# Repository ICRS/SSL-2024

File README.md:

# Robocup 2024 SSL Imperial College London

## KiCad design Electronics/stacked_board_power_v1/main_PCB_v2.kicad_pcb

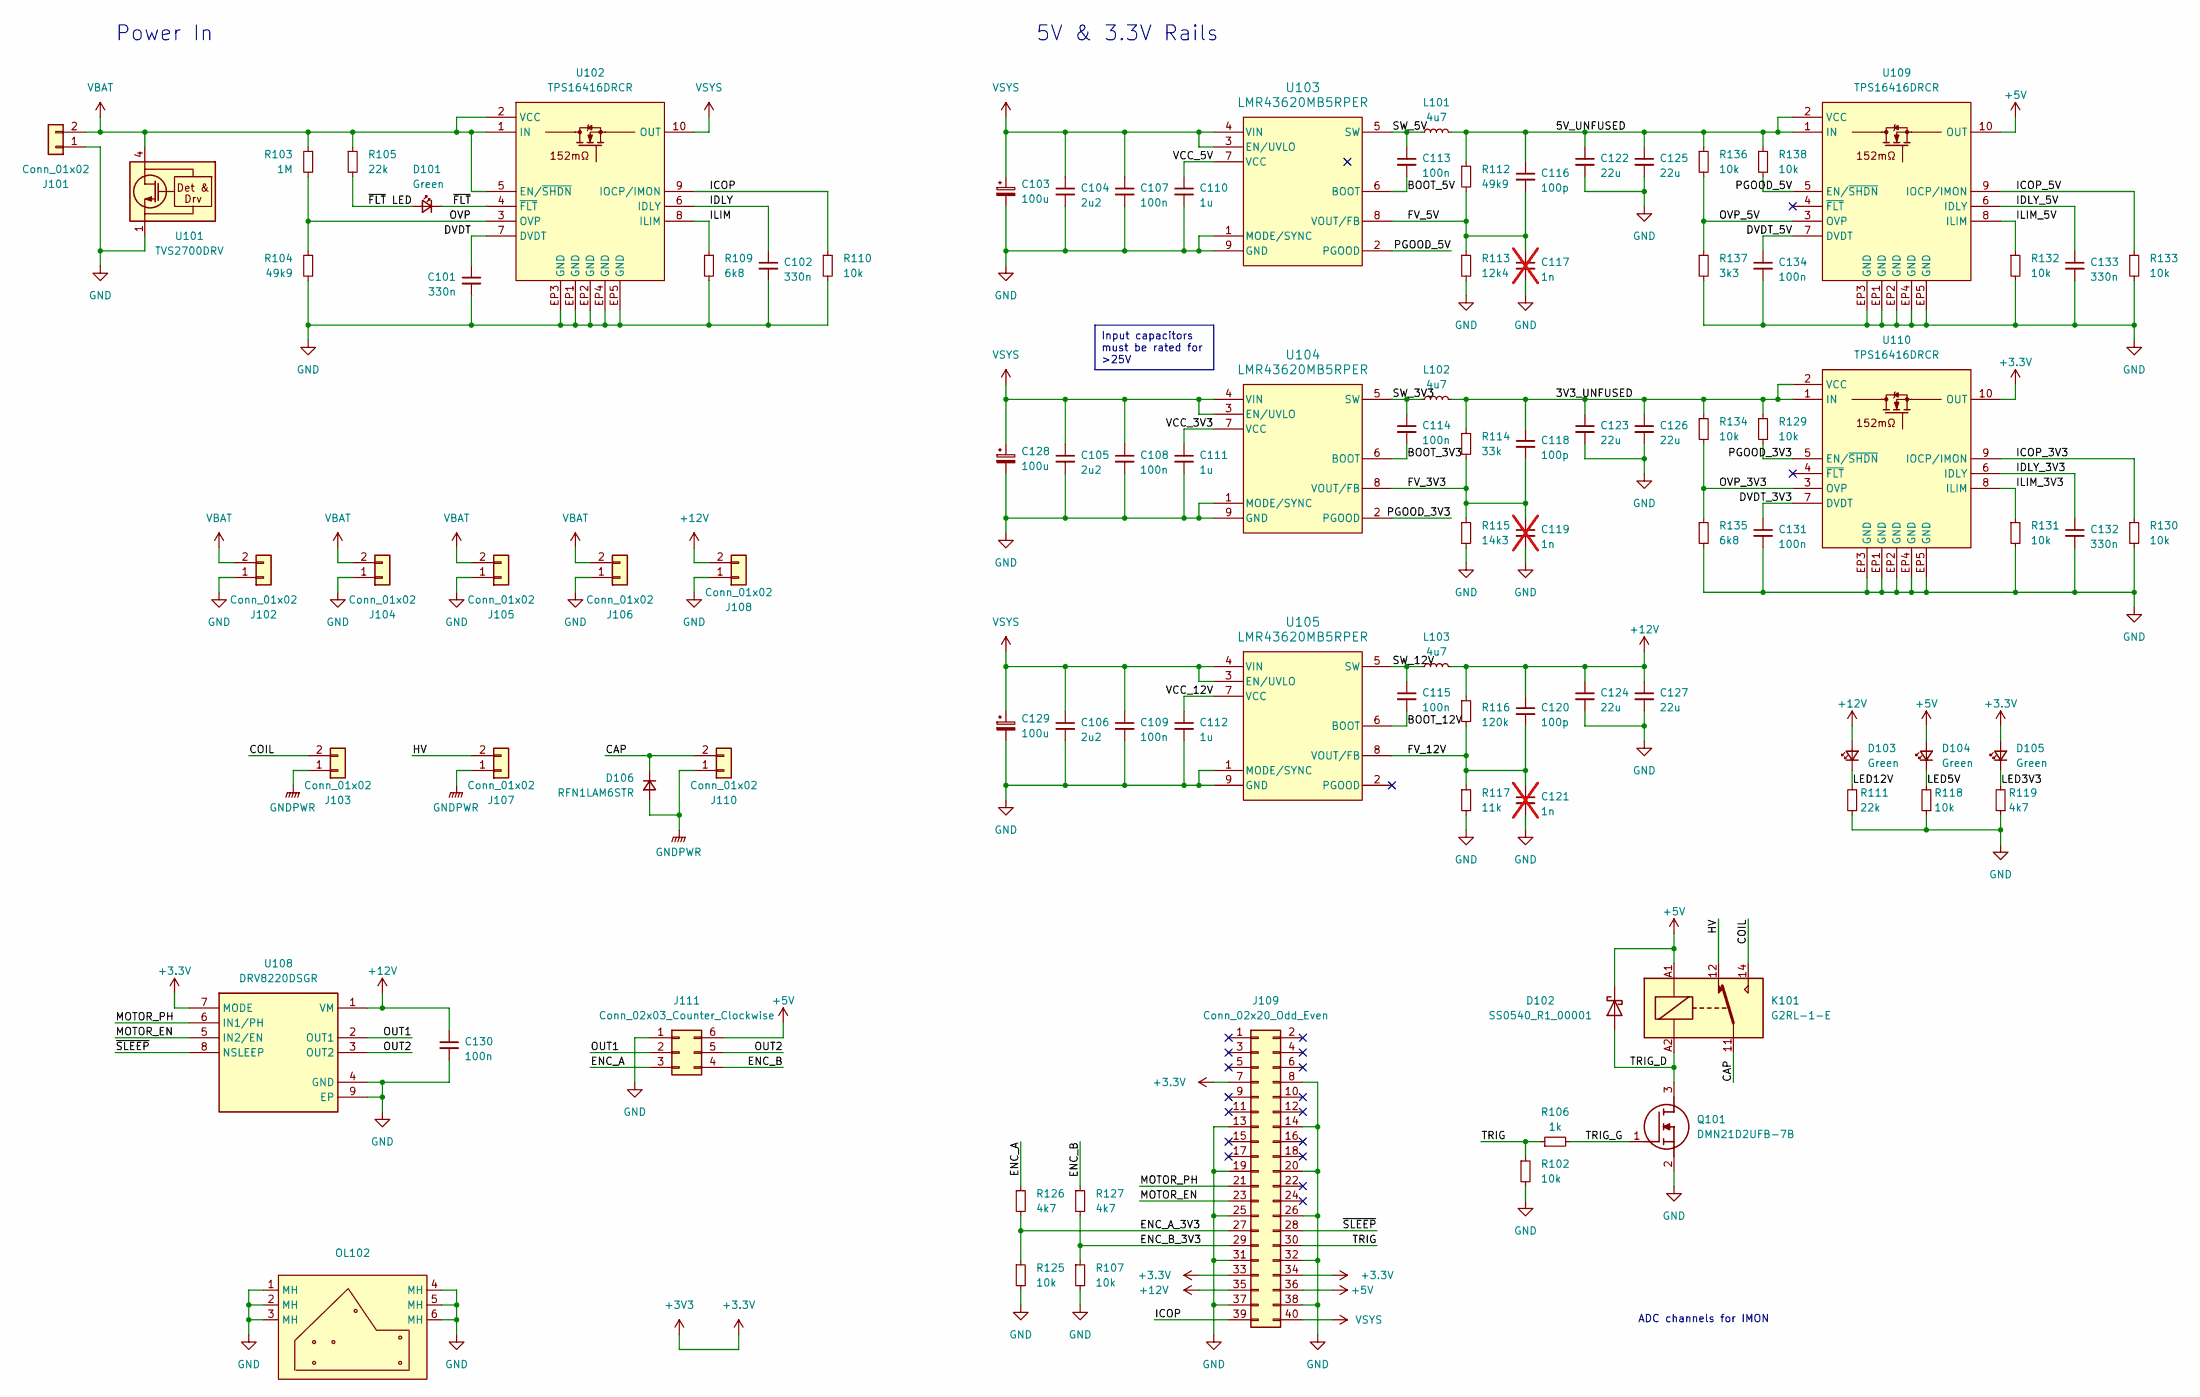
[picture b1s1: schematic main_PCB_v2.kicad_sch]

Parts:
C101, C102, C132, C133: 330n; C_0402_1005Metric
C103, C128, C129: 100u; CP_Elec_6.3x5.9
C104, C105, C106: 2u2; C_0603_1608Metric
C107, C108, C109, C113, C114, C115, C130, C131, C134: 100n; C_0402_1005Metric
C110, C111, C112: 1u; C_0402_1005Metric
C116, C118, C120: 100p; C_0402_1005Metric
C117, C119, C121: 1n; C_0402_1005Metric; not fitted
C122, C123, C124, C125, C126, C127: 22u; C_0603_1608Metric
D101, D103, D104, D105: Green; LED_0402_1005Metric
D102: SS0540_R1_00001; D_SOD-123
D106: RFN1LAM6STR; D_SOD-128
J101: Conn_01x02; AMASS_XT60-M_1x02_P7.20mm_Vertical
J102, J103, J104, J105, J106, J107, J108, J110: Conn_01x02; AMASS_XT30U-F_1x02_P5.0mm_Vertical
J109: Conn_02x20_Odd_Even; PinHeader_2x20_P2.54mm_Vertical
J111: Conn_02x03_Counter_Clockwise; IDC-Header_2x03_P2.54mm_Vertical
K101: G2RL-1-E; Relay_SPDT_Omron_G2RL-1-E
L101, L102, L103: 4u7; L_Chilisin_BMRA00040420
OL102: main_board_outline_v3
Q101: DMN21D2UFB-7B; DMN21D2UFB7B; Mouser Part Number 621-DMN21D2UFB-7B
R102, R107, R110, R118, R125, R129, R130, R131, R132, R133, R134, R136, R138: 10k; R_0402_1005Metric
R103: 1M; R_0402_1005Metric
R104, R112: 49k9; R_0402_1005Metric
R105, R111: 22k; R_0402_1005Metric
R106: 1k; R_0402_1005Metric
R109, R135: 6k8; R_0402_1005Metric
R113: 12k4; R_0402_1005Metric
R114: 33k; R_0402_1005Metric
R115: 14k3; R_0402_1005Metric
R116: 120k; R_0402_1005Metric
R117: 11k; R_0402_1005Metric
R119, R126, R127: 4k7; R_0402_1005Metric
R137: 3k3; R_0402_1005Metric
U101: TVS2700DRV; WSON-6-1EP_2x2mm_P0.65mm_EP1x1.6mm
U102, U109, U110: TPS16416DRCR; TPS74901DRCR; Mouser Part Number 595-TPS16416DRCR
U103, U104, U105: LMR43620MB5RPER; LMR43620MB5RPER_TEX
U108: DRV8220DSGR; SON50P200X200X80-9N; Mouser Part Number 595-DRV8220DSGR

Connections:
+3.3V: D105.2 (A), J109.7, J109.33, J109.34, U108.7 (MODE), U110.10 (OUT)
+5V: D102.1 (K), D104.2 (A), J109.36, J111.6, K101.A1, U109.10 (OUT)
+12V: C120.1, C124.1, C127.1, C130.1, D103.2 (A), J108.2, J109.35, L103.2, R116.1, U108.1 (VM)
/3V3_UNFUSED: C118.1, C123.1, C126.1, L102.2, R114.1, R129.1, R134.1, U110.1 (IN), U110.2 (VCC)
/5V_UNFUSED: C116.1, C122.1, C125.1, L101.2, R112.1, R136.1, R138.1, U109.1 (IN), U109.2 (VCC)
/BOOT_3V3: C114.2, U104.6 (BOOT)
/BOOT_5V: C113.2, U103.6 (BOOT)
/BOOT_12V: C115.2, U105.6 (BOOT)
/CAP: D106.1 (K), J110.2, K101.11
/COIL: J103.2, K101.14
/DVDT: C101.1, U102.7 (DVDT)
/DVDT_3V3: C131.1, U110.7 (DVDT)
/DVDT_5V: C134.1, U109.7 (DVDT)
/ENC_A: J111.3, R126.1
/ENC_A_3V3: J109.27, R125.1, R126.2
/ENC_B: J111.4, R127.1
/ENC_B_3V3: J109.29, R107.1, R127.2
/FV_3V3: C118.2, C119.1, R114.2, R115.1, U104.8 (VOUT/FB)
/FV_5V: C116.2, C117.1, R112.2, R113.1, U103.8 (VOUT/FB)
/FV_12V: C120.2, C121.1, R116.2, R117.1, U105.8 (VOUT/FB)
/HV: J107.2, K101.12
/ICOP: J109.39, R110.1, U102.9 (IOCP/IMON)
/ICOP_3V3: R130.1, U110.9 (IOCP/IMON)
/ICOP_5V: R133.1, U109.9 (IOCP/IMON)
/IDLY: C102.1, U102.6 (IDLY)
/IDLY_3V3: C132.1, U110.6 (IDLY)
/IDLY_5V: C133.1, U109.6 (IDLY)
/ILIM: R109.1, U102.8 (ILIM)
/ILIM_3V3: R131.1, U110.8 (ILIM)
/ILIM_5V: R132.1, U109.8 (ILIM)
/LED3V3: D105.1 (K), R119.2
/LED5V: D104.1 (K), R118.2
/LED12V: D103.1 (K), R111.2
/MOTOR_EN: J109.23, U108.5 (IN2/EN)
/MOTOR_PH: J109.21, U108.6 (IN1/PH)
/OUT1: J111.2, U108.2 (OUT1)
/OUT2: J111.5, U108.3 (OUT2)
/OVP: R103.2, R104.1, U102.3 (OVP)
/OVP_3V3: R134.2, R135.1, U110.3 (OVP)
/OVP_5V: R136.2, R137.1, U109.3 (OVP)
/PGOOD_3V3: R129.2, U104.2 (PGOOD), U110.5 (EN/~SHDN)
/PGOOD_5V: R138.2, U103.2 (PGOOD), U109.5 (EN/~SHDN)
/SW_3V3: C114.1, L102.1, U104.5 (SW)
/SW_5V: C113.1, L101.1, U103.5 (SW)
/SW_12V: C115.1, L103.1, U105.5 (SW)
/TRIG: J109.30, R102.1, R106.1
/TRIG_D: D102.2 (A), K101.A2, Q101.3 (D)
/TRIG_G: Q101.1 (G), R106.2
/VCC_3V3: C111.1, U104.7 (VCC)
/VCC_5V: C110.1, U103.7 (VCC)
/VCC_12V: C112.1, U105.7 (VCC)
/~FLT: D101.1 (K), U102.4 (~FLT)
/~FLT LED: D101.2 (A), R105.2
/~SLEEP: J109.28, U108.8 (NSLEEP)
GND: C101.2, C102.2, C103.2, C104.2, C105.2, C106.2, C107.2, C108.2, C109.2, C110.2, C111.2, C112.2, C117.2, C119.2, C121.2, C122.2, C123.2, C124.2, C125.2, C126.2, C127.2, C128.2, C129.2, C130.2, C131.2, C132.2, C133.2, C134.2, J101.1, J102.1, J104.1, J105.1, J106.1, J108.1, J109.8, J109.13, J109.14, J109.19, J109.20, J109.25, J109.26, J109.31, J109.32, J109.37, J109.38, J111.1, OL102.1 (MH), OL102.2 (MH), OL102.3 (MH), OL102.4 (MH), OL102.5 (MH), OL102.6 (MH), Q101.2 (S), R102.2, R104.2, R107.2, R109.2, R110.2, R111.1, R113.2, R115.2, R117.2, R118.1, R119.1, R125.2, R130.2, R131.2, R132.2, R133.2, R135.2, R137.2, U101.1 (GND), U101.2 (GND), U101.3 (GND), U101.7 (GND), U102.EP1 (GND), U102.EP2 (GND), U102.EP3 (GND), U102.EP4 (GND), U102.EP5 (GND), U103.1 (MODE/SYNC), U103.9 (GND), U104.1 (MODE/SYNC), U104.9 (GND), U105.1 (MODE/SYNC), U105.9 (GND), U108.4 (GND), U108.9 (EP), U109.EP1 (GND), U109.EP2 (GND), U109.EP3 (GND), U109.EP4 (GND), U109.EP5 (GND), U110.EP1 (GND), U110.EP2 (GND), U110.EP3 (GND), U110.EP4 (GND), U110.EP5 (GND)
GNDPWR: D106.2 (A), J103.1, J107.1, J110.1
VBAT: J101.2, J102.2, J104.2, J105.2, J106.2, R103.1, R105.1, U101.4 (IN), U101.5 (IN), U101.6 (IN), U102.1 (IN), U102.2 (VCC), U102.5 (EN/~SHDN)
VSYS: C103.1, C104.1, C105.1, C106.1, C107.1, C108.1, C109.1, C128.1, C129.1, J109.40, U102.10 (OUT), U103.3 (EN/UVLO), U103.4 (VIN), U104.3 (EN/UVLO), U104.4 (VIN), U105.3 (EN/UVLO), U105.4 (VIN)

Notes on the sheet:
Input capacitors must be rated for >25V
Power In
5V & 3.3V Rails
ADC channels for IMON

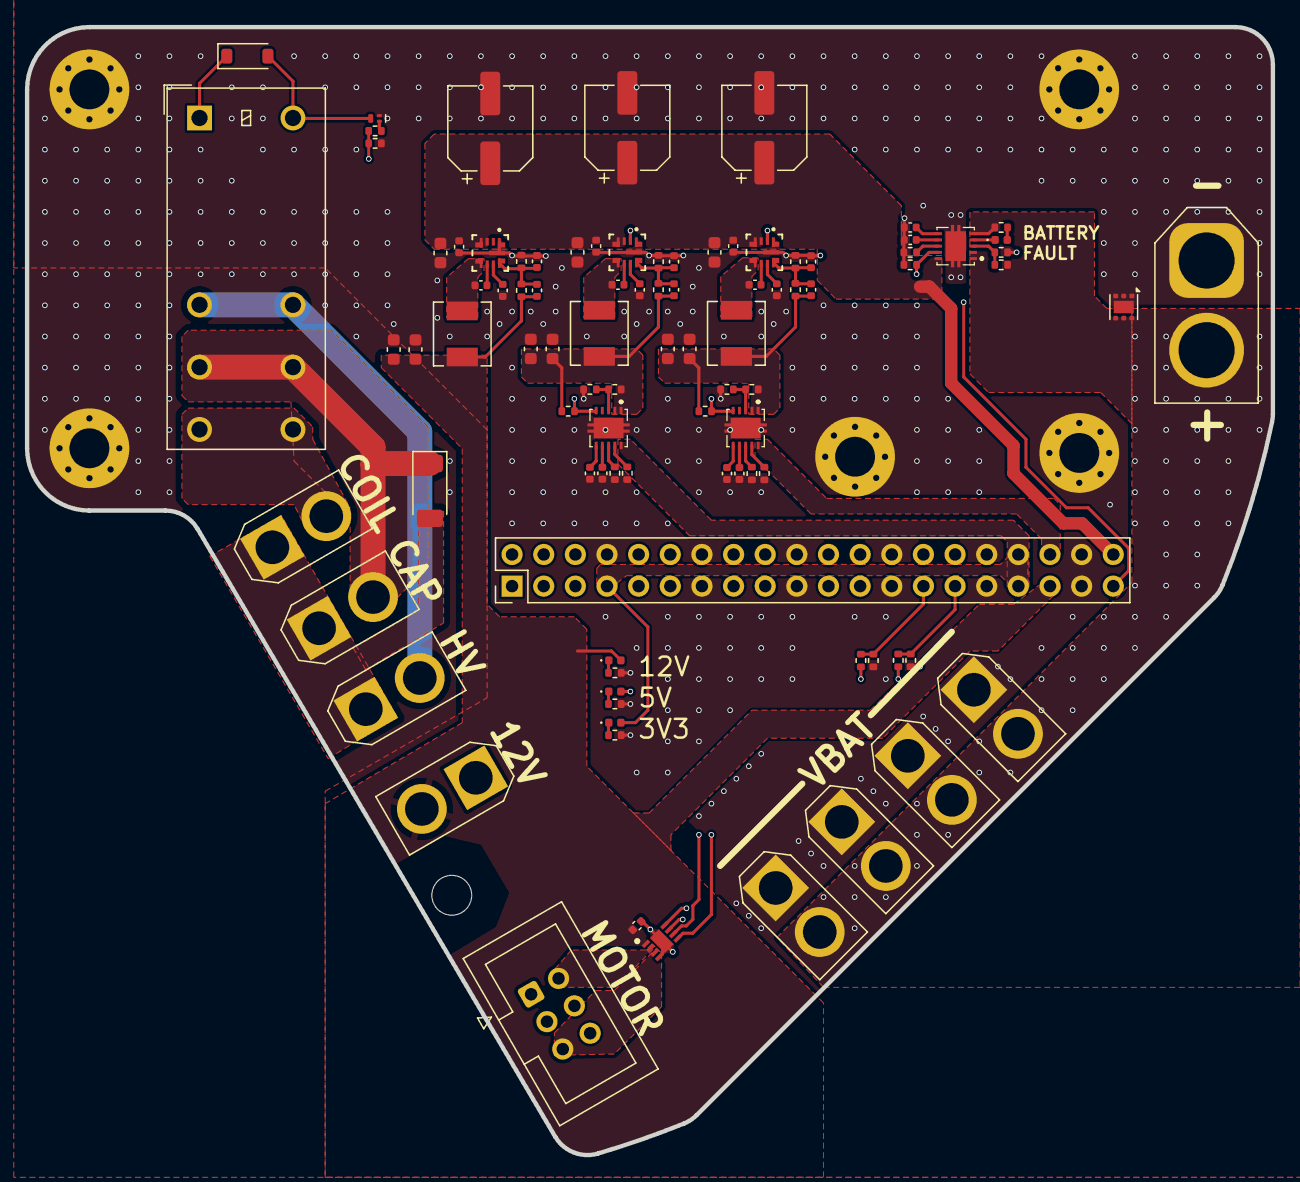
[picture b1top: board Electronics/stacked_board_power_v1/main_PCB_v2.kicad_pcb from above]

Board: 4 copper layers, 100.0 x 90.5 mm, 95 parts (0 on the bottom side), 58 nets.

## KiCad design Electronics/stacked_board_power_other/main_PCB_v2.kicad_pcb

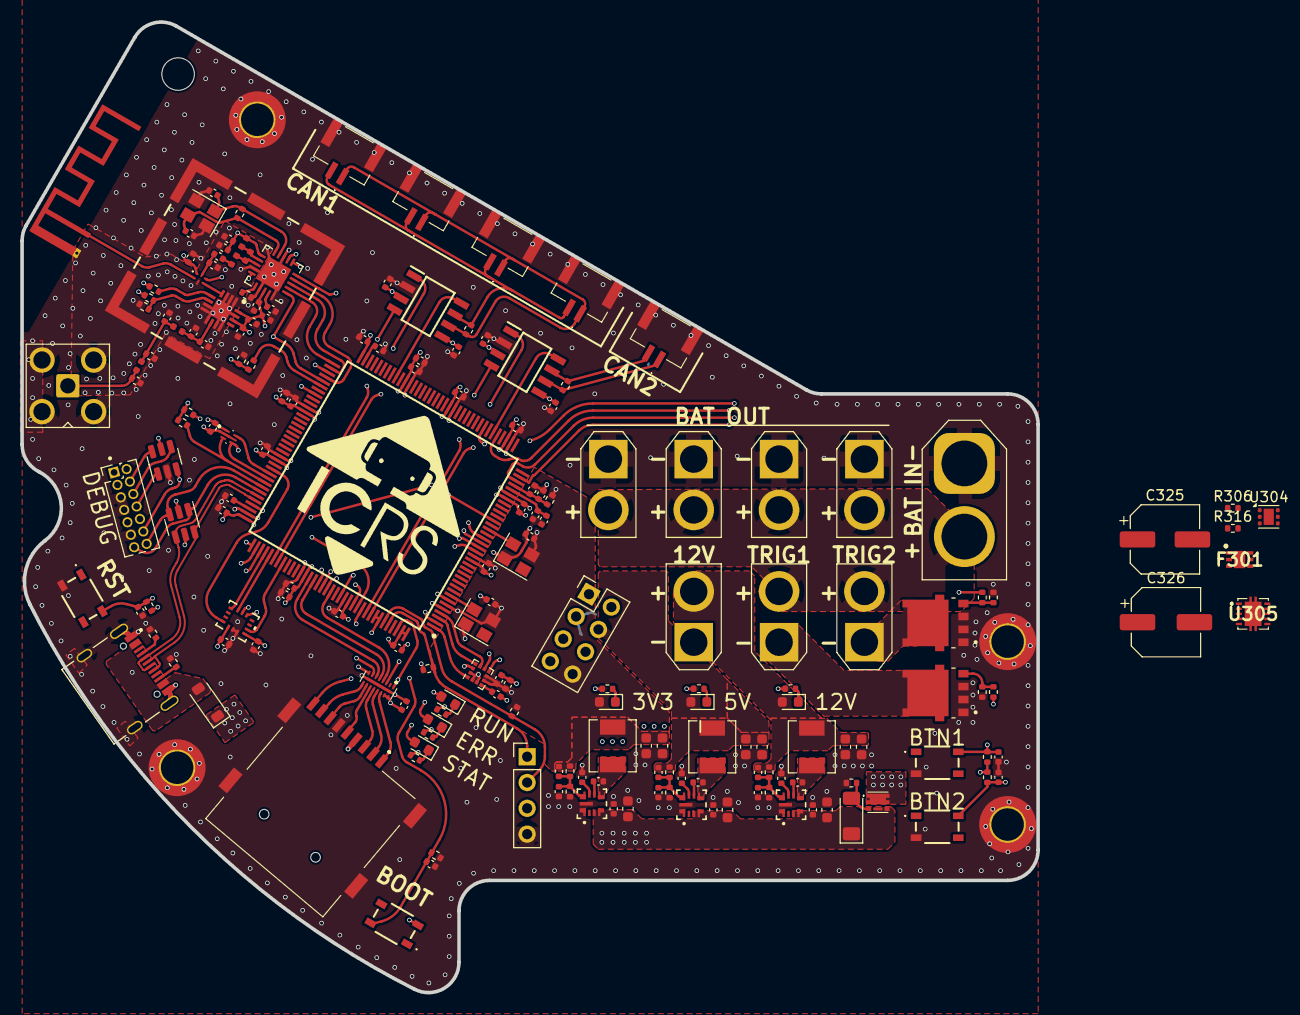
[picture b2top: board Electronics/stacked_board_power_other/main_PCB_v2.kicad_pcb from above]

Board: 4 copper layers, 100.0 x 95.5 mm, 186 parts (0 on the bottom side), 83 nets.

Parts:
AE401: Antenna; Texas_SWRA117D_2.4GHz_Right
C201, C202, C205, C206, C207, C208, C209, C210, C212, C213, C214, C215, C216, C217, C218, C223, C224, C225, C226, C227, C228, C229, C231, C232, C233, C235, C237, C238, C302, C304, C312, C318, C321, C322: 100n; C_0402_1005Metric
C203, C204, C220, C221, C401, C408: 10n; C_0402_1005Metric
C211, C219, C222: 10u; C_0402_1005Metric
C230, C234, C236, C303, C311, C317, C409: 1u; C_0402_1005Metric
C301, C313, C316: 2u2; C_0603_1608Metric
C305, C306, C314, C315, C319, C320: 22u; C_0603_1608Metric
C307, C308, C309: 100p; C_0402_1005Metric
C310, C323, C324, C406: 1n; C_0402_1005Metric
C325: 100u; CP_Elec_6.3x7.7
C326: 100u; CP_Elec_6.3x5.9
C402, C414, C415, C416, C417: 1p5; C_0402_1005Metric
C403: 1p; C_0402_1005Metric
C404: 2n2; C_0402_1005Metric
C405: 4p7; C_0402_1005Metric
C407: 33n; C_0402_1005Metric
C410, C411: 22p; C_0402_1005Metric
C412: 220p; C_0402_1005Metric
C413: 0p3; C_0402_1005Metric
D201: SS0540_R1_00001; D_SOD-123
D202: Red; LED_0603_1608Metric
D203, D301, D302, D304: Green; LED_0603_1608Metric
D204: Blue; LED_0603_1608Metric
D303: ZMM10V; D_MiniMELF
F301: TPS25961DRVR; SON65P200X200X80-7N
FB201: 120R@100MHz; R_0402_1005Metric
FL201: EMIF06-MSD02N16; EMIF06MSD02N16
IC202, IC203: TJA1057GT/3; SOIC127P600X175-8N
J201: MEM2075-00-140-01-A; MEM20750014001A
J203: TYPE-C-31-M-12; HRO_TYPE-C-31-M-12
J204: Conn_02x04_Odd_Even; PinHeader_2x04_P2.54mm_Vertical
J205: Conn_ST_STDC14; PinHeader_2x07_P1.27mm_Vertical
J207: Conn_01x04; PinHeader_1x04_P2.54mm_Vertical
J208, J209, J210, J211, J212: SM02B-GHS-TB_LF__SN_; SM02BGHSTBLFSN
J301: Conn_01x02; AMASS_XT60-M_1x02_P7.20mm_Vertical
J302, J305, J306, J307, J308, J309, J310: Conn_01x02; AMASS_XT30U-F_1x02_P5.0mm_Vertical
J401: Conn_Coaxial; SMA_Amphenol_901-143_Horizontal
L301, L303, L305: 4u7; L_Chilisin_BMRA00040420
L401: 3n9; L_0402_1005Metric
L402, L405: 2n4; L_0402_1005Metric
L403: 8n2; L_0402_1005Metric
L404: 2n7; L_0402_1005Metric
OL101: Main_board_outline_v2; main_board_outline_v2
Q302: DMP3028LFDE; DMP2066UFDE7
R201, R202: 5k1; R_0402_1005Metric
R203, R204, R214, R215, R305: 4k7; R_0402_1005Metric
R205, R206, R207, R210, R304, R314, R315: 10k; R_0402_1005Metric
R208, R209: 120R; R_0402_1005Metric
R211, R212, R213: 2k7; R_0402_1005Metric
R301: 120k; R_0402_1005Metric
R302: 11k; R_0402_1005Metric
R303, R401, R405, R406, R407: 22k; R_0402_1005Metric
R306, R308, R316: 49k9; R_0402_1005Metric
R307: 2k2; R_0402_1005Metric
R309: 12k4; R_0402_1005Metric
R310: 33k; R_0402_1005Metric
R311: 14k3; R_0402_1005Metric
R312, R313: 10R; R_0402_1005Metric
R402: 1M; R_0402_1005Metric
R403, R404: 1k; R_0402_1005Metric
S201, S202, S203, S204: TS20-42-25-WT-160-SMT-TR; TS204225WT160SMTTRMSL
S401: SKY13453-385LF; SKY13453385LF
SH401: SMS-202F; SMS202F
T301, T302: NVMFS4C05NT1G; TRANS_NVMFS5834NLWFT1G
U201: STM32H723ZGT6; QFP50P2200X2200X160-144N
U202, U203: USBLC6-4SC6; SOT-23-6
U204: BMI270; BMI270_BOS
U206: LIS3MDL; LGA-12_2x2mm_P0.5mm
U211: M24C08-FMH6TG; M24C08FMH6TG
U301, U302, U303: LMR43620MB5RPER; LMR43620MB5RPER_TEX
U304: TVS2700DRV; WSON-6-1EP_2x2mm_P0.65mm_EP1x1.6mm
U305: TPS16416DRCR; TPS74901DRCR
U401: NRF24L01; QFN-20-1EP_4x4mm_P0.5mm_EP2.5x2.5mm
U402: RFX2401C; QFN50P300X300X60-17N-D
X201: 25MHz_Clock; Oscillator_SMD_Abracon_ASE-4Pin_3.2x2.5mm
X202: 32.768kHz_Clock; Oscillator_SMD_Abracon_ASE-4Pin_3.2x2.5mm
Y402: 16M; Oscillator_SMD_Abracon_ASE-4Pin_3.2x2.5mm

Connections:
+3.3V: C201.1, C202.1, C205.1, C206.1, C207.1, C208.1, C209.1, C210.1, C211.1, C212.1, C213.1, C214.1, C215.1, C216.1, C217.1, C218.1, C219.1, C222.1, C223.1, C224.1, C225.1, C228.1, C229.1, C230.1, C232.1, C308.1, C319.1, C320.1, C401.2, C406.2, C408.2, C409.2, C412.2, D304.2 (A), FB201.2, FL201.15 (VCC), FL201.16 (RDATA_VCC), IC202.5 (VIO), IC203.5 (VIO), J201.4 (VDD), J204.8, J205.3 (VCC), J207.3, L303.2, R203.1, R204.1, R205.2, R206.2, R210.2, R214.1, R215.1, R310.1, S202.3 (COM_1), S401.1 (VDD), U201.6 (VBAT), U201.17 (VDD), U201.30 (VDD), U201.39 (VDD), U201.52 (VDD), U201.62 (VDD), U201.72 (VDD), U201.84 (VDD), U201.95 (VDD33USB), U201.108 (VDD), U201.121 (VDD), U201.131 (VDD), U201.143 (PDR_ON), U201.144 (VDD), U202.5 (VBUS), U204.5 (VDDIO), U204.8 (VDD), U206.5 (Vdd), U206.6 (Vdd_IO), U211.1 (VCC), U401.7 (VDD), U401.15 (VDD), U401.18 (VDD), U402.14 (VDD_1), U402.16 (VDD_2), X201.3 (OUT), X202.3 (OUT)
+5V: C226.1, C227.1, C309.1, C314.1, C315.1, D302.2 (A), IC202.3 (VCC), IC203.3 (VCC), J204.4, L305.2, R308.1
+12V: C305.1, C306.1, C307.1, D301.2 (A), J302.2, L301.2, R301.1
/Microcontroller/BOOT: C220.1, R207.2, S202.2 (NO_2)
/Microcontroller/BTN1: C204.1, R206.1, S201.2 (NO_2)
/Microcontroller/BTN2: C221.1, R210.1, S204.2 (NO_2)
/Microcontroller/CAN1_H: IC202.7 (CANH), J208.2, J209.2, J210.2, J211.2, R209.1
/Microcontroller/CAN1_L: IC202.6 (CANL), J208.1, J209.1, J210.1, J211.1, R209.2
/Microcontroller/CAN2_H: IC203.7 (CANH), J212.2, R208.1
/Microcontroller/CAN2_L: IC203.6 (CANL), J212.1, R208.2
/Microcontroller/CC1: J203.A5 (CC1), R201.1
/Microcontroller/CC2: J203.B5 (CC2), R202.1
/Microcontroller/CLK: FL201.11 (CLK_EX), J201.5 (CLK)
/Microcontroller/CMD: FL201.12 (CMD_EX), J201.3 (CMD)
/Microcontroller/DAT0: FL201.10 (DAT0_EX), J201.7 (DAT0)
/Microcontroller/DAT1: FL201.9 (DAT1_EX), J201.8 (DAT1)
/Microcontroller/DAT2: FL201.14 (DAT2_EX), J201.1 (DAT2)
/Microcontroller/DAT3: FL201.13 (DAT3_EX), J201.2 (CD/DAT3)
/Microcontroller/I2C1_SCL: J207.2, R204.2
/Microcontroller/I2C1_SDA: J207.1, R203.2
/Microcontroller/I2C3_SCL: R214.2, U211.3 (SDA)
/Microcontroller/I2C3_SDA: R215.2, U211.4 (SCL)
/Microcontroller/LEDB_K: D204.1 (K), R213.2
/Microcontroller/LEDG_K: D203.1 (K), R212.2
/Microcontroller/LEDR_K: D202.1 (K), R211.2
/Microcontroller/MAG_C1: C231.1, U206.4 (C1)
/Microcontroller/NRF24_CE: R404.1, U401.1 (CE)
/Microcontroller/NRST: C203.1, J205.12 (~RST), R205.1, S203.2 (NO_2), U202.3 (I/O2)
/Microcontroller/SDMMC2_CD: FL201.1 (WP/CD), J201.9 (CD)
/Microcontroller/SWCLK: J205.6 (JCLK/SWCLK), U202.4 (I/O3)
/Microcontroller/SWDIO: J205.4 (JTMS/SWDIO), U202.6 (I/O4)
/Microcontroller/SWO: J205.8 (JTDO/SWO), U202.1 (I/O1)
/Microcontroller/USART1_RX: J205.13 (VCP_RX), U203.1 (I/O1)
/Microcontroller/USART1_TX: J205.14 (VCP_TX), U203.3 (I/O2)
/Microcontroller/USB_DN: J203.A7 (DN1), J203.B7 (DN2), U203.4 (I/O3)
/Microcontroller/USB_DP: J203.A6 (DP1), J203.B6 (DP2), U203.6 (I/O4)
/Microcontroller/VCAP1: C237.1, U201.71 (VCAP)
/Microcontroller/VCAP2: C238.1, U201.106 (VCAP)
/Microcontroller/VDDA: C233.1, C234.1, FB201.1, U201.33 (VDDA)
/Microcontroller/VREF+: C235.1, C236.1, U201.32 (VREF+)
/Power/BOOT_3V3: C318.2, U302.6 (BOOT)
/Power/BOOT_5V: C312.2, U301.6 (BOOT)
/Power/BOOT_12V: C304.2, U303.6 (BOOT)
/Power/FV_3V3: C308.2, C323.1, R310.2, R311.1, U302.8 (VOUT/FB)
/Power/FV_5V: C309.2, C324.1, R308.2, R309.1, U301.8 (VOUT/FB)
/Power/FV_12V: C307.2, C310.1, R301.2, R302.1, U303.8 (VOUT/FB)
/Power/LED3V3: D304.1 (K), R305.2
/Power/LED5V: D302.1 (K), R304.2
/Power/LED12V: D301.1 (K), R303.2
/Power/RP_PMOS_G: D303.2 (A), Q302.3 (G), R307.1
/Power/SW_3V3: C318.1, L303.1, U302.5 (SW)
/Power/SW_5V: C312.1, L305.1, U301.5 (SW)
/Power/SW_12V: C304.1, L301.1, U303.5 (SW)
/Power/TRIG1_D: J309.1, T302.5_6 (D)
/Power/TRIG1_G: R312.1, R315.1, T302.4 (G)
/Power/TRIG2_D: J310.1, T301.5_6 (D)
/Power/TRIG2_G: R313.1, R314.1, T301.4 (G)
/Power/VCC_3V3: C317.1, U302.7 (VCC)
/Power/VCC_5V: C311.1, U301.7 (VCC)
/Power/VCC_12V: C303.1, U303.7 (VCC)
/Wireless/ANT1: L403.2, L404.1, U401.12 (ANT1)
/Wireless/ANT2: L401.2, L403.1, U401.13 (ANT2)
/Wireless/ANT2_50: C402.2, L401.1
/Wireless/ANT_F1: C413.2, C414.2, L402.2, U402.10 (ANT)
/Wireless/ANT_F2: C415.2, C416.2, L402.1, L405.2
/Wireless/ANT_PCB: AE401.1 (A), S401.2 (RF1)
/Wireless/ANT_SMA: C417.2, J401.1 (In), L405.1
/Wireless/DVDD: C407.2, U401.19 (DVDD)
/Wireless/IREF: R401.1, U401.16 (IREF)
/Wireless/RF2: S401.4 (RF2), U402.4 (TXRX)
/Wireless/RFC: C402.1, C403.2, S401.6 (RFC)
/Wireless/RXEN: R404.2, R405.1, U402.6 (RXEN)
/Wireless/TXEN: R403.2, U402.5 (TXEN)
/Wireless/VCTL: R406.2, R407.1, S401.5 (VCTL)
/Wireless/VDD_PA: C404.2, C405.2, L404.2, R403.1, U401.11 (VDD_PA)
/Wireless/XC1: C410.1, R402.1, U401.10 (XC1), Y402.3
/Wireless/XC2: C411.1, R402.2, U401.9 (XC2), Y402.1
GND: AE401.2 (Shield), C201.2, C202.2, C203.2, C204.2, C205.2, C206.2, C207.2, C208.2, C209.2, C210.2, C211.2, C212.2, C213.2, C214.2, C215.2, C216.2, C217.2, C218.2, C219.2, C220.2, C221.2, C222.2, C223.2, C224.2, C225.2, C226.2, C227.2, C228.2, C229.2, C230.2, C231.2, C232.2, C233.2, C234.2, C235.2, C236.2, C237.2, C238.2, C301.2, C302.2, C303.2, C305.2, C306.2, C310.2, C311.2, C313.2, C314.2, C315.2, C316.2, C317.2, C319.2, C320.2, C321.2, C322.2, C323.2, C324.2, C401.1, C403.1, C404.1, C405.1, C406.1, C407.1, C408.1, C409.1, C410.2, C411.2, C412.1, C413.1, C414.1, C415.1, C416.1, C417.1, FL201.17 (EP_(GND)), IC202.2 (GND), IC203.2 (GND), J201.6 (VSS), J201.10 (MP1), J201.11 (MP2), J201.12 (MP3), J201.13 (MP4), J203.A1_B12 (GND), J203.B1_A12 (GND), J203.S1 (SHIELD), J203.S2 (SHIELD), J203.S3 (SHIELD), J203.S4 (SHIELD), J204.3, J204.7, J205.5 (GND), J205.7 (GND), J205.11 (GNDDetect), J207.4, J208.3, J208.4, J209.3, J209.4, J210.3, J210.4, J211.3, J211.4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
unnamed: Q302.1 (D_1), Q302.2 (D_2), Q302.5 (D_3), Q302.6 (D_4), Q302.8 (D_5)
unnamed: R306.2, R316.1, U305.3 (OVP)
VBAT: J301.2, J305.2, J306.2, J307.2, J308.2, J309.2, J310.2, R306.1, U304.4 (IN), U304.5 (IN), U304.6 (IN), U305.1 (IN), U305.2 (VCC)
VBUS: D201.2 (A), J203.A4_B9 (VBUS), J203.B4_A9 (VBUS), U203.5 (VBUS)
VSYS: C301.1, C302.1, C313.1, C316.1, C321.1, C322.1, D201.1 (K), D303.1 (K), Q302.4 (S_1), Q302.7 (S_2), U301.3 (EN/UVLO), U301.4 (VIN), U302.3 (EN/UVLO), U302.4 (VIN), U303.3 (EN/UVLO), U303.4 (VIN)

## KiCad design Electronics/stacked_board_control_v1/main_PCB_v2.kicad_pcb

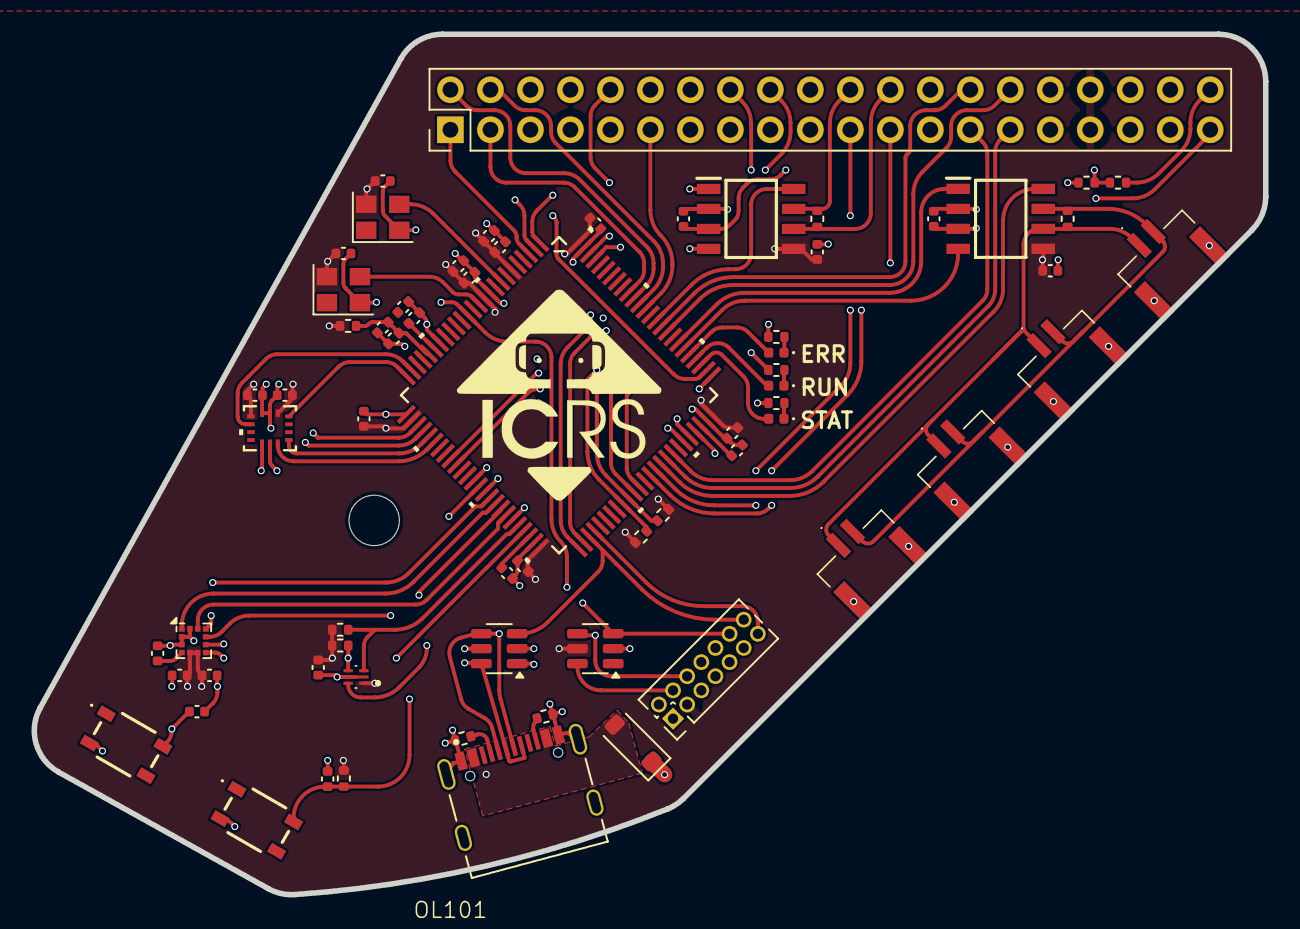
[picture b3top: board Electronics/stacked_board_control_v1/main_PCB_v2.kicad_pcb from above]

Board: 4 copper layers, 78.2 x 54.7 mm, 67 parts (0 on the bottom side), 75 nets.

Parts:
C101, C102, C103, C104, C109, C110, C111, C112, C113, C114, C115, C116, C118, C122, C126, C133, C134, C136, C137: 100n; C_0402_1005Metric
C105, C106: 10n; C_0402_1005Metric
C117, C121, C124, C138: 1u; C_0402_1005Metric
C119: 4u7; C_0402_1005Metric
C120, C123: 2u2; C_0402_1005Metric
D101: Red; LED_0402_1005Metric
D102: Green; LED_0402_1005Metric
D103: Blue; LED_0402_1005Metric
D104: SS0540_R1_00001; D_SOD-123
FB101: 120R@100MHz; R_0402_1005Metric
IC101, IC102: TJA1057GT/3; SOIC127P600X175-8N
J101, J102, J103, J104: SM02B-GHS-TB_LF__SN_; SM02BGHSTBLFSN
J108: TYPE-C-31-M-12; HRO_TYPE-C-31-M-12
J110: 20021112-00014T1LF; PinHeader_2x07_P1.27mm_Vertical
J112: Conn_02x20_Odd_Even; PinHeader_2x20_P2.54mm_Vertical
OL101: daughter_board_outline_v1
R101, R102: 120R; R_0402_1005Metric
R103, R104, R106, R109: 4k7; R_0402_1005Metric
R105, R108: 10k; R_0402_1005Metric
R107: 100k; R_0402_1005Metric
R111, R112, R113: 2k7; R_0402_1005Metric
R114, R115: 5k1; R_0402_1005Metric
S101, S102: TS20-42-25-WT-160-SMT-TR; TS204225WT160SMTTRMSL
U101: STM32H723VGT6
U102: M24C08-FMH6TG; M24C08FMH6TG
U103, U105: USBLC6-4SC6; SOT-23-6
U106: BMI270; BMI270_BOS
U107: LIS3MDL; LGA-12_2x2mm_P0.5mm
X101: 25MHz_Clock; Oscillator_SMD_Abracon_ASE-4Pin_3.2x2.5mm
X102: 32.768kHz_Clock; Oscillator_SMD_Abracon_ASE-4Pin_3.2x2.5mm

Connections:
+3.3V: C101.1, C103.1, C109.1, C110.1, C111.1, C112.1, C113.1, C114.1, C115.1, C116.1, C117.1, C119.1, C122.1, C133.1, C134.1, C137.1, C138.1, FB101.2, IC101.5 (VIO), IC102.5 (VIO), J110.3 (VCC), J112.7, J112.33, J112.34, R103.1, R104.1, R105.2, R106.1, R109.1, U101.6 (VBAT), U101.11 (VDD), U101.27 (VDD), U101.50 (VDD), U101.75 (VDD), U101.100 (VDD), U102.1 (VCC), U105.5 (VBUS), U106.5 (VDDIO), U106.8 (VDD), U107.5 (Vdd), U107.6 (Vdd_IO), X101.4 (VDD), X102.4 (VDD)
+5V: C102.1, C104.1, IC101.3 (VCC), IC102.3 (VCC), J112.36
/BTN: C106.1, R105.1, S102.2 (NO_2), U101.38 (PE8)
/CAN1_H: IC101.7 (CANH), J101.2, J102.2, J103.2, J104.2, R101.1
/CAN1_L: IC101.6 (CANL), J101.1, J102.1, J103.1, J104.1, R101.2
/CAN1_RX: IC101.4 (RXD), U101.81 (PD0)
/CAN1_SILENT: IC101.8 (S), U101.66 (PC9)
/CAN1_TX: IC101.1 (TXD), U101.82 (PD1)
/CAN2_H: IC102.7 (CANH), J112.22, R102.1
/CAN2_L: IC102.6 (CANL), J112.24, R102.2
/CAN2_RX: IC102.4 (RXD), U101.51 (PB12)
/CAN2_SILENT: IC102.8 (S), U101.86 (PD5)
/CAN2_TX: IC102.1 (TXD), U101.52 (PB13)
/CC1: J108.A5 (CC1), R114.1
/CC2: J108.B5 (CC2), R115.1
/EEPROM_WC: U101.45 (PE15), U102.5 (~WC)
/ENC_A: J112.27, U101.68 (PA9)
/ENC_B: J112.29, U101.67 (PA8)
/GPIO1: J112.11, U101.88 (PD7)
/GPIO2: J112.16, U101.61 (PD14)
/GPIO3: J112.18, U101.62 (PD15)
/I2C2_SCL: R103.2, U101.46 (PB10), U102.3 (SDA)
/I2C2_SDA: R106.2, U101.47 (PB11), U102.4 (SCL)
/I2C4_SCL: J112.15, R104.2, U101.59 (PD12)
/I2C4_SDA: J112.17, R109.2, U101.60 (PD13)
/IMU_INT1: U101.25 (PA3), U106.4 (INT1)
/IMU_INT2: U101.24 (PA2), U106.9 (INT2)
/ISYS_ADC: J112.39, U101.35 (PB1)
/LEDB: D103.2 (A), U101.78 (PC10)
/LEDB_K: D103.1 (K), R113.2
/LEDG: D102.2 (A), U101.79 (PC11)
/LEDG_K: D102.1 (K), R112.2
/LEDR: D101.2 (A), U101.80 (PC12)
/LEDR_K: D101.1 (K), R111.2
/MAG_C1: C136.1, U107.4 (C1)
/MAG_DRDY: U101.39 (PE9), U107.8 (DRDY)
/MAG_INT: U101.40 (PE10), U107.7 (INT)
/MOTOR_EN: J112.23, U101.64 (PC7)
/MOTOR_PH: J112.21, U101.65 (PC8)
/NRF24_CE: J112.6, U101.2 (PE3)
/NRF24_IRQ: J112.1, U101.3 (PE4)
/NRF24_MODE: J112.9, U101.1 (PE2)
/NRST: C105.1, J110.12 (~RST), S101.2 (NO_2), U101.14 (NRST), U105.3 (I/O2)
/OSC: U101.12 (PH0-OSC_IN), X101.3 (OUT)
/OSC_32: U101.8 (PC14-OSC32_IN), X102.3 (OUT)
/SPI1_CS: U101.28 (PA4), U106.12 (CSB)
/SPI1_MISO: U101.30 (PA6), U106.1 (SDO)
/SPI1_MOSI: U101.31 (PA7), U106.14 (SDX)
/SPI1_SCK: U101.29 (PA5), U106.13 (SCX)
/SPI3_CS: J112.5, U101.77 (PA15)
/SPI3_MISO: J112.2, U101.90 (PB4)
/SPI3_MOSI: J112.3, U101.91 (PB5)
/SPI3_SCK: J112.4, U101.89 (PB3)
/SPI4_CS: U101.41 (PE11), U107.10 (~CS)
/SPI4_MISO: U101.43 (PE13), U107.9 (SDO/SA1)
/SPI4_MOSI: U101.44 (PE14), U107.11 (SDA/SDI/SDO)
/SPI4_SCK: U101.42 (PE12), U107.1 (SCL/SPC)
/SWCLK: J110.6 (JCLK/SWCLK), U101.76 (PA14), U105.4 (I/O3)
/SWDIO: J110.4 (JTMS/SWDIO), U101.72 (PA13), U105.6 (I/O4)
/TRIG: J112.30, U101.84 (PD3)
/UART8_RX: J112.12, U101.97 (PE0)
/UART8_TX: J112.10, U101.98 (PE1)
/USART1_RX: J110.13 (VCP_RX), U101.54 (PB15), U103.1 (I/O1)
/USART1_TX: J110.14 (VCP_TX), U101.53 (PB14), U103.3 (I/O2)
/USB_DN: J108.A7 (DN1), J108.B7 (DN2), U101.70 (PA11), U103.4 (I/O3)
/USB_DP: J108.A6 (DP1), J108.B6 (DP2), U101.71 (PA12), U103.6 (I/O4)
/VCAP1: C120.1, U101.48 (VCAP)
/VCAP2: C123.1, U101.73 (VCAP)
/VDDA: C118.1, C121.1, FB101.1, U101.21 (VDDA)
/VREF+: C124.1, C126.1, U101.20 (VREF+)
/VSYS_ADC: R107.2, R108.1, U101.34 (PB0)
/~SLEEP: J112.28, U101.85 (PD4)
GND: C101.2, C102.2, C103.2, C104.2, C105.2, C106.2, C109.2, C110.2, C111.2, C112.2, C113.2, C114.2, C115.2, C116.2, C117.2, C118.2, C119.2, C120.2, C121.2, C122.2, C123.2, C124.2, C126.2, C133.2, C134.2, C136.2, C137.2, C138.2, IC101.2 (GND), IC102.2 (GND), J101.3, J101.4, J102.3, J102.4, J103.3, J103.4, J104.3, J104.4, J108.A1_B12 (GND), J108.B1_A12 (GND), J108.S1 (SHIELD), J108.S2 (SHIELD), J108.S3 (SHIELD), J108.S4 (SHIELD), J110.5 (GND), J110.7 (GND), J110.11 (GNDDetect), J112.8, J112.13, J112.14, J112.19, J112.20, J112.25, J112.26, J112.31, J112.32, J112.37, J112.38, R108.2, R111.1, R112.1, R113.1, R114.2, R115.2, S101.3 (COM_1), S102.3 (COM_1), U101.10 (VSS), U101.19 (VSSA), U101.26 (VSS), U101.49 (VSS), U101.74 (VSS), U101.99 (VSS), U102.2 (VSS), U103.2 (GND), U105.2 (GND), U106.6 (GNDIO), U106.7 (GND), U107.2 (GND), U107.3 (GND), U107.12 (GND), X101.2 (GND), X102.2 (GND)
VBUS: D104.2 (A), J108.A4_B9 (VBUS), J108.B4_A9 (VBUS), U103.5 (VBUS)
VSYS: D104.1 (K), J112.40, R107.1

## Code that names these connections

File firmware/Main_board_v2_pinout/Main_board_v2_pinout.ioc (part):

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Mcu.Name=STM32H723VGTx
Mcu.Package=LQFP100
Mcu.UserName=STM32H723VGTx
PA11.Mode=Device_Only_FS
PA11.Signal=USB_OTG_HS_DM
PA12.Mode=Device_Only_FS
PA12.Signal=USB_OTG_HS_DP
PA13(JTMS/SWDIO).Mode=Serial_Wire
PA13(JTMS/SWDIO).Signal=DEBUG_JTMS-SWDIO
PA14(JTCK/SWCLK).Mode=Serial_Wire
PA14(JTCK/SWCLK).Signal=DEBUG_JTCK-SWCLK
PA15(JTDI).Mode=NSS_Signal_Hard_Output
PA15(JTDI).Signal=SPI3_NSS
PA2.GPIOParameters=GPIO_Label
PA2.GPIO_Label=IMU_INT2
PA2.Signal=GPXTI2
PA3.GPIOParameters=GPIO_Label
PA3.GPIO_Label=IMU_INT1
PA3.Signal=GPXTI3
PA4.Mode=NSS_Signal_Hard_Output
PA4.Signal=SPI1_NSS
PA5.Mode=Full_Duplex_Master
PA5.Signal=SPI1_SCK
PA6.Mode=Full_Duplex_Master
PA6.Signal=SPI1_MISO
PA7.Mode=Full_Duplex_Master
PA7.Signal=SPI1_MOSI
PA8.Signal=S_TIM1_CH1
PA9.Signal=S_TIM1_CH2
PB0.Signal=ADCx_INP9
PB1.Signal=ADCx_INP5
PB10.Mode=I2C
PB10.Signal=I2C2_SCL
PB11.Mode=I2C
PB11.Signal=I2C2_SDA
PB12.Mode=FDCAN_Activate
PB12.Signal=FDCAN2_RX
PB13.Mode=FDCAN_Activate
PB13.Signal=FDCAN2_TX
PB14.Mode=Asynchronous
PB14.Signal=USART1_TX
PB15.Mode=Asynchronous
PB15.Signal=USART1_RX
PB3(JTDO/TRACESWO).Mode=Full_Duplex_Master
PB3(JTDO/TRACESWO).Signal=SPI3_SCK
PB4(NJTRST).Mode=Full_Duplex_Master
PB4(NJTRST).Signal=SPI3_MISO
PB5.Mode=Full_Duplex_Master
PB5.Signal=SPI3_MOSI
PC14-OSC32_IN.Mode=LSE-External-Clock-Source
PC14-OSC32_IN.Signal=RCC_OSC32_IN
PC7.Signal=S_TIM3_CH2
PC8.Signal=S_TIM3_CH3
PC9.GPIOParameters=GPIO_Label
PC9.GPIO_Label=FDCAN1_SILENT
PC9.Signal=GPIO_Output
PD0.Mode=FDCAN_Activate
PD0.Signal=FDCAN1_RX
PD1.Mode=FDCAN_Activate
PD1.Signal=FDCAN1_TX
PD12.Mode=I2C
PD12.Signal=I2C4_SCL
PD13.Mode=I2C
PD13.Signal=I2C4_SDA
PD14.Signal=GPIO_Input
PD15.Signal=GPIO_Input
PD3.GPIOParameters=GPIO_Label
PD3.GPIO_Label=TRIG
PD3.Signal=GPIO_Output
PD4.GPIOParameters=GPIO_Label
PD4.GPIO_Label=nSLEEP
PD4.Signal=GPIO_Output
PD5.GPIOParameters=GPIO_Label
PD5.GPIO_Label=FDCAN2_SILENT
PD5.Signal=GPIO_Output
PE0.Mode=Asynchronous
PE0.Signal=UART8_RX
PE1.Mode=Asynchronous
PE1.Signal=UART8_TX
PE10.GPIOParameters=GPIO_Label
PE10.GPIO_Label=MAG_INT
PE10.Signal=GPXTI10
PE11.Mode=NSS_Signal_Hard_Output
PE11.Signal=SPI4_NSS
PE12.Mode=Full_Duplex_Master
PE12.Signal=SPI4_SCK
PE13.Mode=Full_Duplex_Master
PE13.Signal=SPI4_MISO
PE14.Mode=Full_Duplex_Master
PE14.Signal=SPI4_MOSI
PE15.GPIOParameters=GPIO_Label
PE15.GPIO_Label=EEPROM_WC
PE15.Signal=GPIO_Output
PE2.GPIOParameters=GPIO_Label
PE2.GPIO_Label=NRF24_MODE
PE2.Signal=GPIO_Output
PE3.GPIOParameters=GPIO_Label
PE3.GPIO_Label=NRF24_CE
PE3.Signal=GPIO_Output
PE4.GPIOParameters=GPIO_Label
PE4.GPIO_Label=NRF24_IRQ
PE4.Signal=GPXTI4
PE9.GPIOParameters=GPIO_Label
PE9.GPIO_Label=MAG_DRDY
PE9.Signal=GPXTI9
PH0-OSC_IN.Mode=HSE-External-Clock-Source
PH0-OSC_IN.Signal=RCC_OSC_IN
RCC.SYSCLKFreq_VALUE=64000000
board=custom

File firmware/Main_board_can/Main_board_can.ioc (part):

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Mcu.Name=STM32H723ZGTx
Mcu.Package=LQFP144
Mcu.UserName=STM32H723ZGTx
PA0.GPIOParameters=GPIO_Label
PA0.GPIO_Label=BTN1
PA0.Signal=GPIO_Input
PA1.GPIOParameters=GPIO_Label
PA1.GPIO_Label=TRIG2
PA1.Signal=GPIO_Output
PA10.Mode=Asynchronous
PA10.Signal=USART1_RX
PA11.Signal=USB_OTG_HS_DM
PA12.Signal=USB_OTG_HS_DP
PA13(JTMS/SWDIO).Mode=Trace_Asynchronous_SW
PA13(JTMS/SWDIO).Signal=DEBUG_JTMS-SWDIO
PA14(JTCK/SWCLK).Mode=Trace_Asynchronous_SW
PA14(JTCK/SWCLK).Signal=DEBUG_JTCK-SWCLK
PA15(JTDI).Mode=NSS_Signal_Hard_Output
PA15(JTDI).Signal=SPI3_NSS
PA5.GPIOParameters=GPIO_Label
PA5.GPIO_Label=TRIG1
PA5.Signal=GPIO_Output
PA6.GPIOParameters=GPIO_PuPd,GPIO_Label
PA6.GPIO_Label=CAN2_SILENT
PA6.GPIO_PuPd=GPIO_PULLUP
PA6.Signal=GPIO_Output
PA8.Mode=I2C
PA8.Signal=I2C3_SCL
PA9.Mode=Asynchronous
PA9.Signal=USART1_TX
PB12.Mode=NSS_Signal_Hard_Output
PB12.Signal=SPI2_NSS
PB13.Mode=Full_Duplex_Master
PB13.Signal=SPI2_SCK
PB14.Mode=Full_Duplex_Master
PB14.Signal=SPI2_MISO
PB15.Mode=Full_Duplex_Master
PB15.Signal=SPI2_MOSI
PB3(JTDO/TRACESWO).Mode=Trace_Asynchronous_SW
PB3(JTDO/TRACESWO).Signal=DEBUG_JTDO-SWO
PB4(NJTRST).GPIOParameters=GPIO_Label
PB4(NJTRST).GPIO_Label=LED_B
PB4(NJTRST).Signal=GPIO_Output
PB5.Mode=FDCAN_Activate
PB5.Signal=FDCAN2_RX
PB6.Mode=FDCAN_Activate
PB6.Signal=FDCAN2_TX
PB7.GPIOParameters=GPIO_Label
PB7.GPIO_Label=BOOT
PB7.Signal=GPIO_Input
PB8.Mode=I2C
PB8.Signal=I2C1_SCL
PB9.Mode=I2C
PB9.Signal=I2C1_SDA
PC10.Mode=Full_Duplex_Master
PC10.Signal=SPI3_SCK
PC11.Mode=Full_Duplex_Master
PC11.Signal=SPI3_MISO
PC12.Mode=Full_Duplex_Master
PC12.Signal=SPI3_MOSI
PC13.GPIOParameters=GPIO_Label
PC13.GPIO_Label=MAG_INT
PC13.Signal=GPXTI13
PC14-OSC32_IN.Signal=RCC_OSC32_IN
PC4.GPIOParameters=GPIO_Label
PC4.GPIO_Label=BTN2
PC4.Signal=GPXTI4
PC7.GPIOParameters=GPIO_Label
PC7.GPIO_Label=IMU_INT1
PC7.Signal=GPXTI7
PC8.GPIOParameters=GPIO_PuPd,GPIO_Label
PC8.GPIO_Label=EEPROM_WC
PC8.GPIO_PuPd=GPIO_PULLUP
PC8.Signal=GPIO_Output
PC9.Mode=I2C
PC9.Signal=I2C3_SDA
PD0.Mode=FDCAN_Activate
PD0.Signal=FDCAN1_RX
PD1.Mode=FDCAN_Activate
PD1.Signal=FDCAN1_TX
PD11.GPIOParameters=GPIO_Label
PD11.GPIO_Label=NRF24_IRQ
PD11.Signal=GPXTI11
PD2.GPIOParameters=GPIO_Label
PD2.GPIO_Label=IMU_INT2
PD2.Signal=GPXTI2
PD6.Signal=SDMMC2_CK
PD7.Signal=SDMMC2_CMD
PD8.GPIOParameters=GPIO_Label
PD8.GPIO_Label=NRF24_CE
PD8.Signal=GPIO_Output
PD9.GPIOParameters=GPIO_Label
PD9.GPIO_Label=NRF24_MODE
PD9.Signal=GPIO_Output
PE1.GPIOParameters=GPIO_Label
PE1.GPIO_Label=SDMMC2_CD
PE1.Signal=GPIO_Input
PE11.GPIOParameters=GPIO_PuPd,GPIO_Label
PE11.GPIO_Label=CAN1_SILENT
PE11.GPIO_PuPd=GPIO_PULLUP
PE11.Signal=GPIO_Output
PE2.Mode=Full_Duplex_Master
PE2.Signal=SPI4_SCK
PE3.GPIOParameters=GPIO_Label
PE3.GPIO_Label=MAG_DRDY
PE3.Signal=GPXTI3
PE4.Mode=NSS_Signal_Hard_Output
PE4.Signal=SPI4_NSS
PE5.Mode=Full_Duplex_Master
PE5.Signal=SPI4_MISO
PE6.Mode=Full_Duplex_Master
PE6.Signal=SPI4_MOSI
PF6.GPIOParameters=GPIO_Label
PF6.GPIO_Label=GPIO3
PF6.Signal=GPIO_Input
PF7.GPIOParameters=GPIO_Label
PF7.GPIO_Label=GPIO4
PF7.Signal=GPIO_Input
PF8.GPIOParameters=GPIO_Label
PF8.GPIO_Label=GPIO2
PF8.Signal=GPIO_Input
PF9.GPIOParameters=GPIO_Label
PF9.GPIO_Label=GPIO1
PF9.Signal=GPIO_Input
PG10.Signal=SDMMC2_D1
PG11.Signal=SDMMC2_D2
PG12.Signal=SDMMC2_D3
PG15.GPIOParameters=GPIO_Label
PG15.GPIO_Label=LED_G
PG15.Signal=GPIO_Output
PG9.Signal=SDMMC2_D0
PH0-OSC_IN.Signal=RCC_OSC_IN
RCC.HSE_VALUE=25000000
RCC.SYSCLKFreq_VALUE=550000000
RCC.SYSCLKSource=RCC_SYSCLKSOURCE_PLLCLK
board=custom

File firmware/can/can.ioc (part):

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Mcu.Name=STM32F407I(E-G)Hx
Mcu.Package=UFBGA176
Mcu.UserName=STM32F407IGHx
PA13.Mode=Serial_Wire
PA13.Signal=SYS_JTMS-SWDIO
PA14.Mode=Serial_Wire
PA14.Signal=SYS_JTCK-SWCLK
PB12.GPIOParameters=GPIO_Label
PB12.GPIO_Label=NRF_CSN
PB12.Signal=GPIO_Output
PB13.Mode=Full_Duplex_Master
PB13.Signal=SPI2_SCK
PB14.Mode=Full_Duplex_Master
PB14.Signal=SPI2_MISO
PB15.Mode=Full_Duplex_Master
PB15.Signal=SPI2_MOSI
PB5.Mode=CAN_Activate
PB5.Signal=CAN2_RX
PB6.Mode=CAN_Activate
PB6.Signal=CAN2_TX
PC6.Mode=Half_duplex(single_wire_mode)
PC6.Signal=USART6_TX
PD0.Mode=CAN_Activate
PD0.Signal=CAN1_RX
PD1.Mode=CAN_Activate
PD1.Signal=CAN1_TX
PF0.GPIOParameters=GPIO_Label
PF0.GPIO_Label=NRF_CE
PF0.Signal=GPIO_Output
PF1.GPIOParameters=GPIO_Label
PF1.GPIO_Label=NRF_IRQ
PF1.Signal=GPXTI1
PH0-OSC_IN.Mode=HSE-External-Oscillator
PH0-OSC_IN.Signal=RCC_OSC_IN
PH1-OSC_OUT.Mode=HSE-External-Oscillator
PH1-OSC_OUT.Signal=RCC_OSC_OUT
PH10.GPIOParameters=PinState,GPIO_PuPd,GPIO_Label
PH10.GPIO_Label=LED_B
PH10.GPIO_PuPd=GPIO_PULLUP
PH10.PinState=GPIO_PIN_SET
PH10.Signal=GPIO_Output
PH11.GPIOParameters=PinState,GPIO_PuPd,GPIO_Label,GPIO_ModeDefaultOutputPP
PH11.GPIO_Label=LED_G
PH11.GPIO_ModeDefaultOutputPP=GPIO_MODE_OUTPUT_PP
PH11.GPIO_PuPd=GPIO_PULLUP
PH11.PinState=GPIO_PIN_SET
PH11.Signal=GPIO_Output
PH12.GPIOParameters=PinState,GPIO_PuPd,GPIO_Label
PH12.GPIO_Label=LED_R
PH12.GPIO_PuPd=GPIO_PULLUP
PH12.PinState=GPIO_PIN_SET
PH12.Signal=GPIO_Output
RCC.HSE_VALUE=12000000
RCC.SYSCLKFreq_VALUE=168000000
RCC.SYSCLKSource=RCC_SYSCLKSOURCE_PLLCLK
board=custom

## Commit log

2023-11-01 updated gitignore
2023-11-01 Added basic test code
2023-11-02 Added drivebase Tasks
2023-11-07 Added CAN motor test and updated old_drivebase_test
2023-11-07 Added TODOs
2023-11-08 Added SSL_Motor_Set_Speed_All()
2023-11-09 Testing CAN receiving
2023-11-09 Encoder data working over CAN
2023-11-22 PID thing
2023-11-22 cool stuff
2024-01-24 Added nRF24
2024-01-29 Big PCB progress
2024-01-29 mechanical section added
2024-01-29 add front image
2024-01-29 Added 12V rail to PCB
2024-01-30 PCB Finished
2024-02-01 Added "Commands.xlsx"
2024-02-07 Updated buck feedback values
2024-02-07 Updated PCB footprints
2024-02-10 RC24 Mech updated prototype
2024-02-14 Qualification video done
2024-02-14 Added main board firmware project
2024-02-14 Created main board v2 PCB project
2024-02-15 New board requirements
2024-02-17 Updated PCB outlines
2024-03-24 pcb progress
2024-03-24 power pcb schematic done
2024-03-24 Power board done
2024-03-25 PCBs Done
